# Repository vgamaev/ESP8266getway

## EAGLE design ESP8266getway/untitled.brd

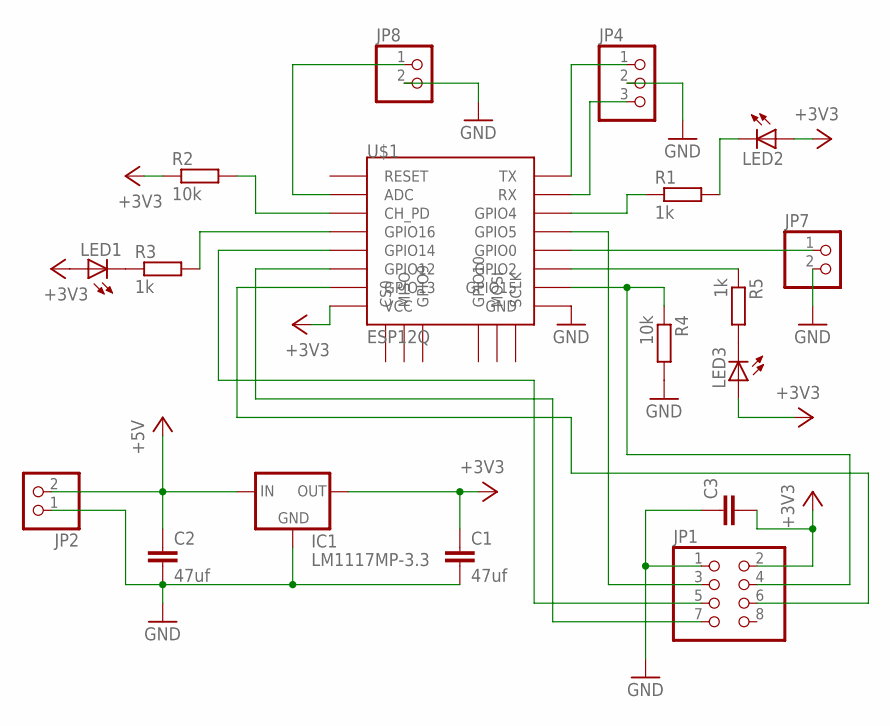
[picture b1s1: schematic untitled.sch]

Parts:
C1, C2: 47uf; C1812K
C3: C-EUC3216; C3216
IC1: LM1117MP-3.3; SOT223
JP1: PINHD-2X4; 2X04
JP2, JP7, JP8: PINHD-1X2; 1X02
JP4: PINHD-1X3; 1X03
LED1, LED2, LED3: LEDSFH482; SFH482
R1, R3, R5: 1k; R0805
R2: 10k; 0207/12
R4: 10k; M0805
U$1: ESP12Q

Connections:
+3V3: C1.1, C3.2, IC1.2 (OUT), IC1.4 (OUT), JP1.2, LED1.A, LED2.A, LED3.A, R2.1, U$1.VCC
+5V: C2.1, IC1.3 (IN), JP2.2
GND: C1.2, C2.2, C3.1, IC1.1 (GND), JP1.1, JP2.1, JP4.2, JP7.2, JP8.2, R4.2, U$1.GND
unnamed: JP1.3, U$1.GPIO5
unnamed: JP1.4, R4.1, U$1.GPIO15
unnamed: JP7.1, U$1.GPIO0
unnamed: R3.2, U$1.GPIO16
unnamed: JP1.5, U$1.GPIO14
unnamed: JP1.7, U$1.GPIO12
unnamed: R2.2, U$1.CH_PD
unnamed: LED1.K (C), R3.1
unnamed: JP1.6, U$1.GPIO13
unnamed: R5.1, U$1.GPIO2
unnamed: LED3.K (C), R5.2
unnamed: LED2.K (C), R1.2
unnamed: JP4.3, U$1.RX
unnamed: JP4.1, U$1.TX
unnamed: JP8.1, U$1.ADC
unnamed: R1.1, U$1.GPIO4

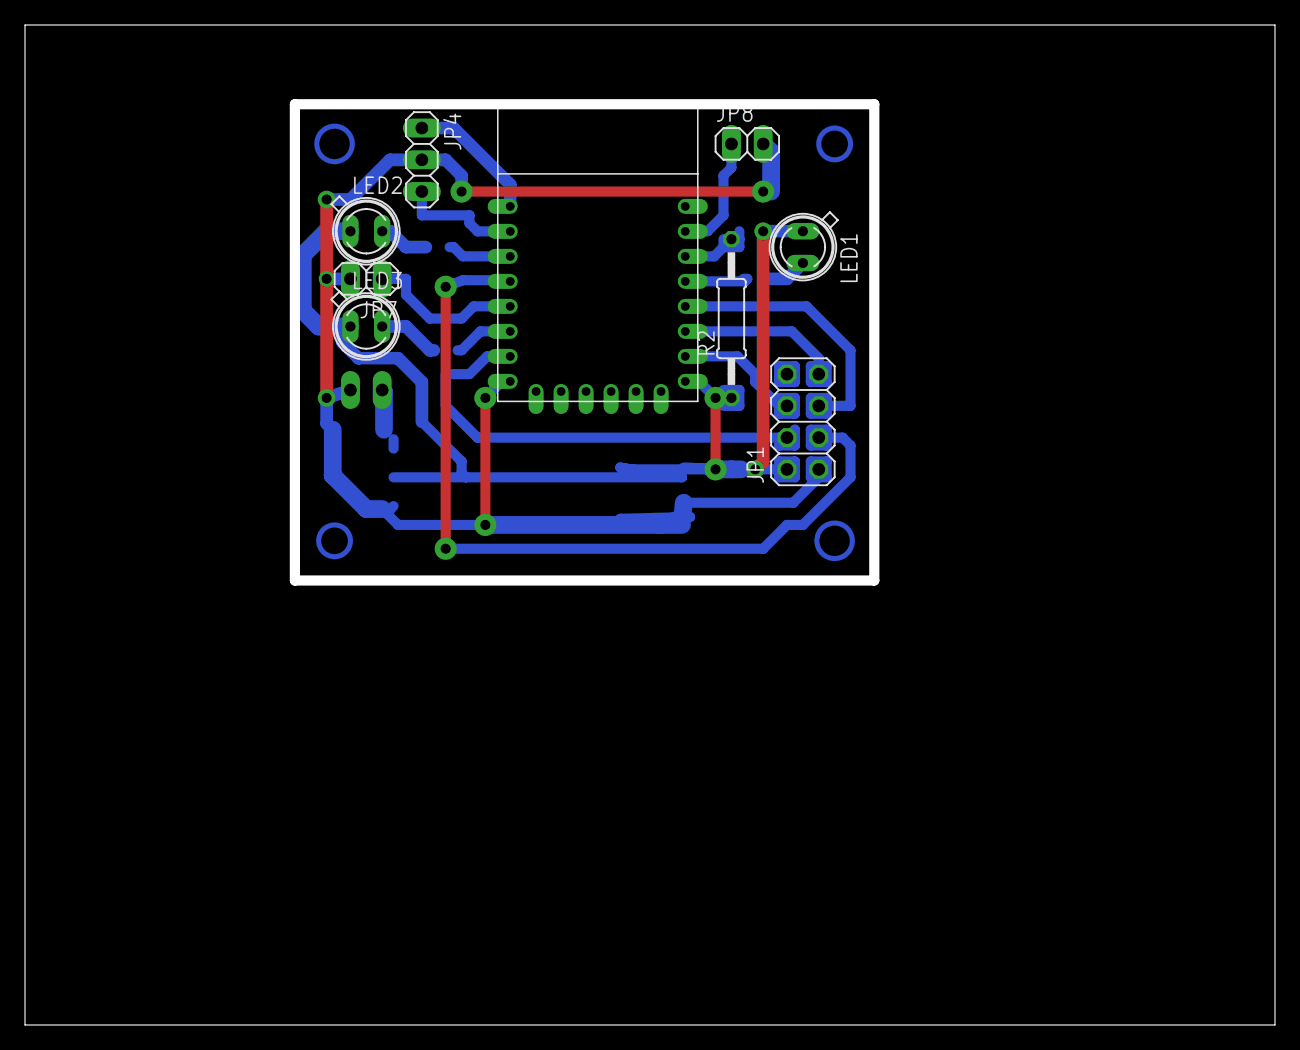
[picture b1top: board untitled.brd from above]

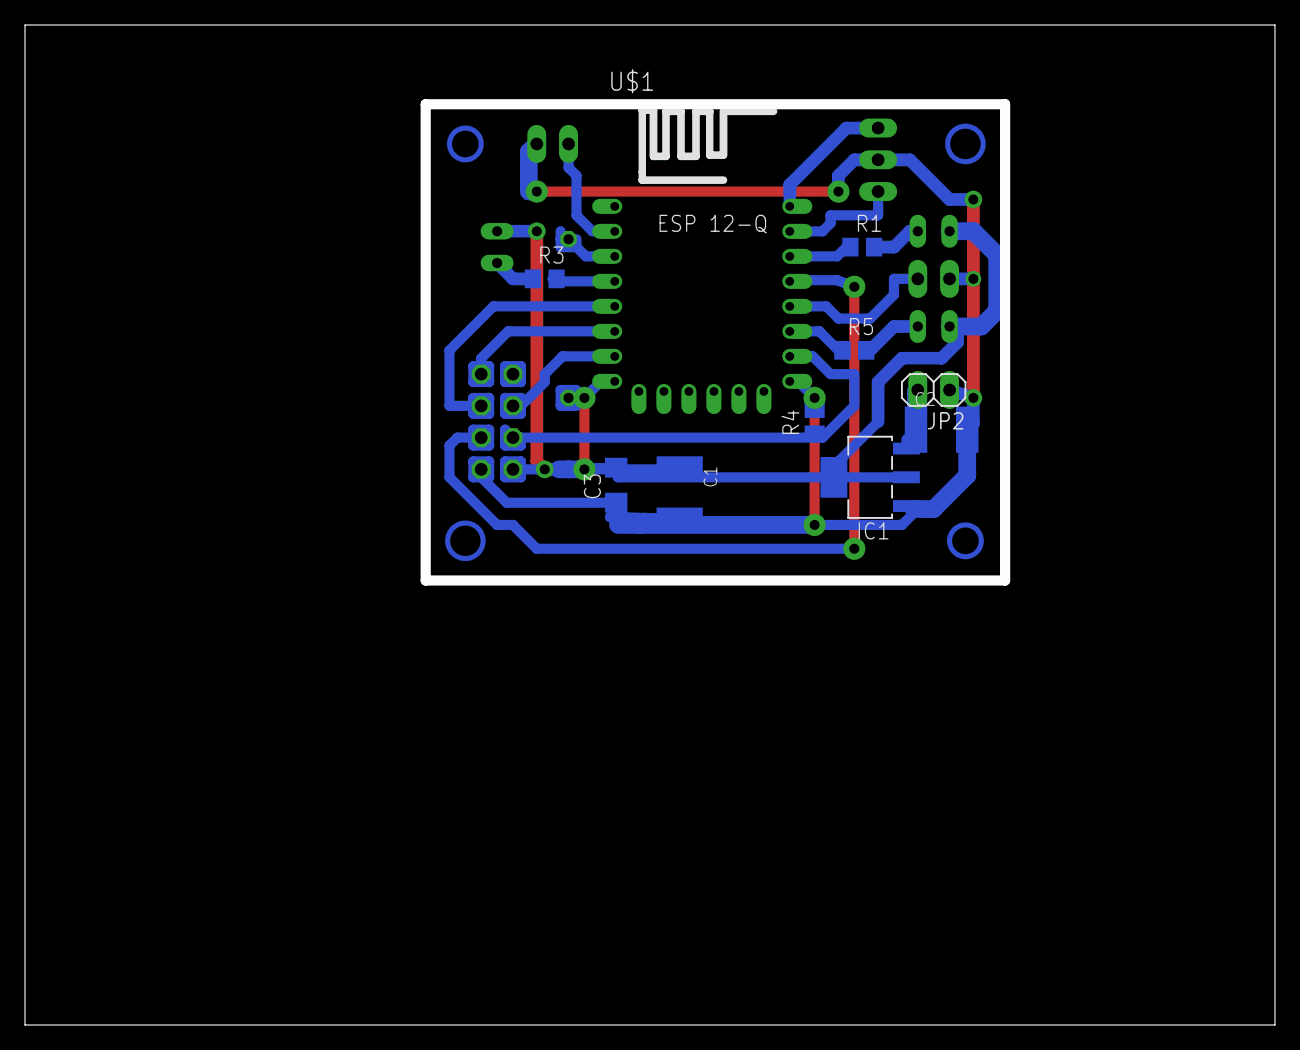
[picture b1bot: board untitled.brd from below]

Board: 2 copper layers, 100.0 x 80.0 mm, 18 parts (10 on the bottom side), 19 nets.

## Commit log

2017-08-26 :octocat: Added .gitattributes & .gitignore files
2017-08-30 30082017
2017-09-02 2092017
2017-09-07 07092017
